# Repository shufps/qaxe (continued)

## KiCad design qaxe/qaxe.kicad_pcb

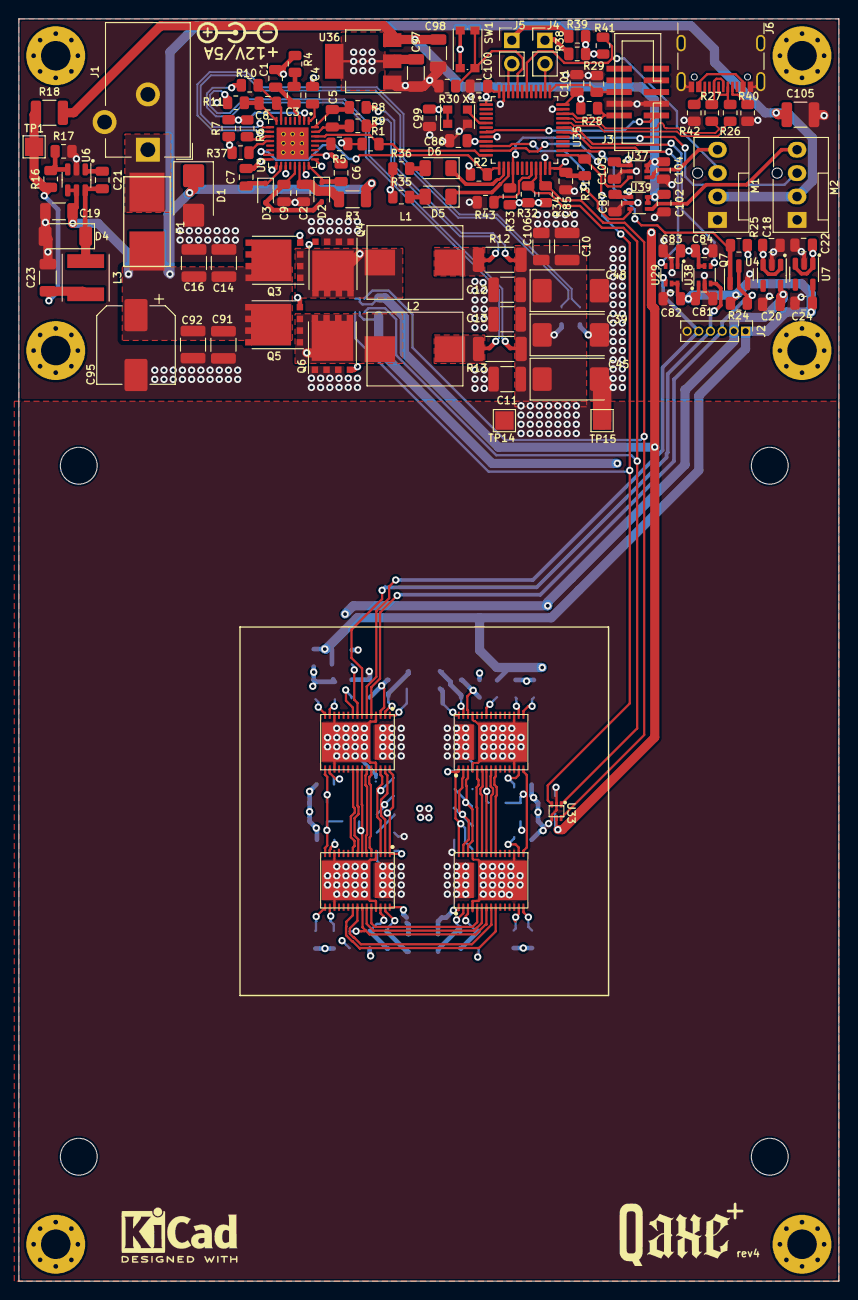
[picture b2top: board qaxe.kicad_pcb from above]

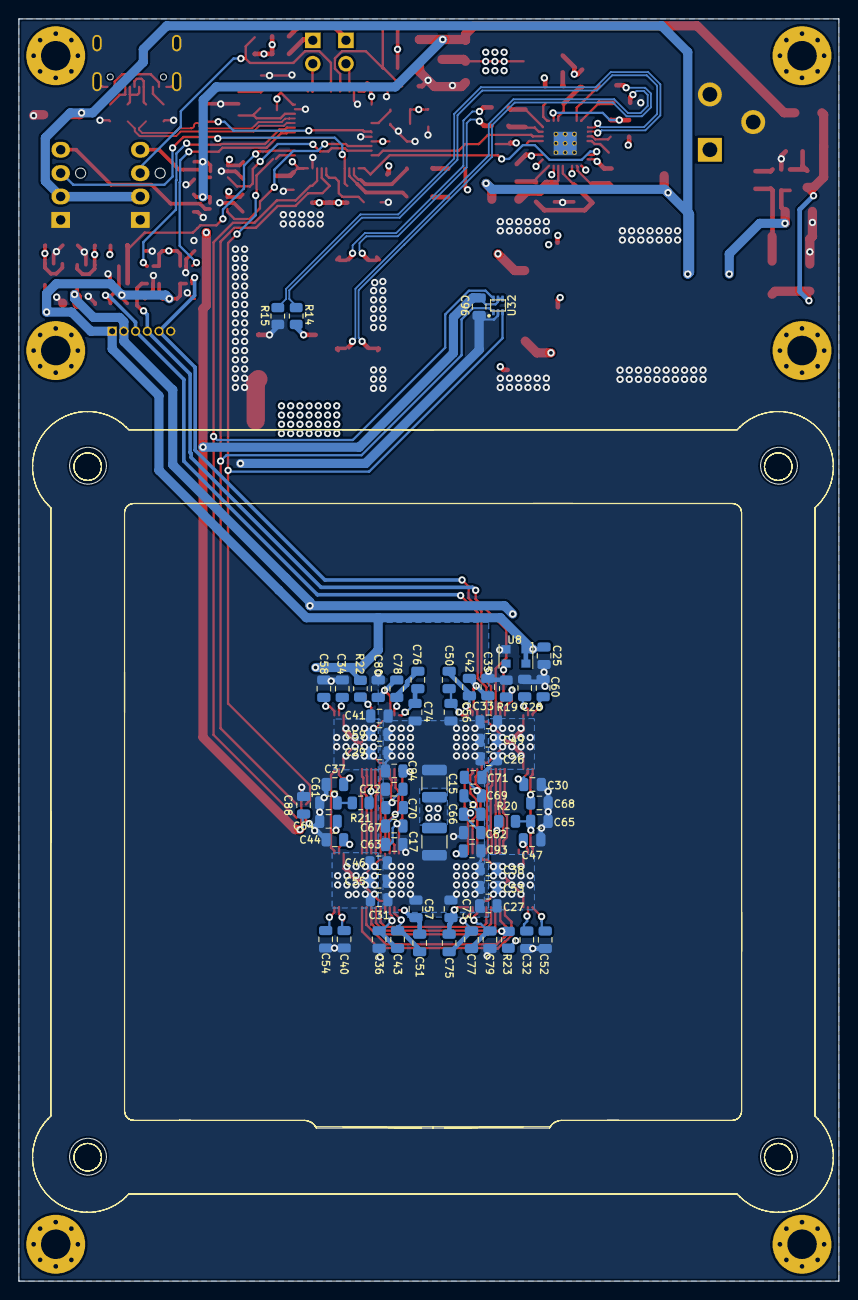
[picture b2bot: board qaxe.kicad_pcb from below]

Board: 4 copper layers, 89.0 x 137.0 mm, 198 parts (68 on the bottom side), 116 nets.

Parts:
C1: 47p; C_0805_2012Metric
C2, C4, C6, C7, C18, C22, C25, C49, C53, C55, C59, C81, C82, C83, C84, C85, C86, C87, C88, C96, C99, C100, C101, C102, C103, C104: 100n; C_0805_2012Metric
C3: 3.3n; C_0805_2012Metric
C5, C8: 1n; C_0805_2012Metric
C9: 4.7µ/25V; C_0805_2012Metric
C10, C11, C12, C13, C15, C17: 100µ/6.3V; C_1210_3225Metric
C14, C16, C91, C92, C105: 22µ/25V; C_1210_3225Metric
C19, C98: 10µF/50V; C_1206_3216Metric
C20, C24, C28, C30, C32, C33, C34, C35, C36, C37, C38, C40, C41, C42, C43, C44, C46, C47, C50, C51, C52, C54, C56, C57, C58, C60, C61, C62, C63, C64, C65, C66, C67, C68, C69, C70, C71, C72, C73, C74, C75, C76, C77, C78, C79, C80, C93, C94: 1µ; C_0805_2012Metric
C21: 10n/250V; C_0805_2012Metric
C23, C97: 22µ/16V; C_1206_3216Metric
C26, C27, C29, C31: 10µ/16V; C_0805_2012Metric
C39, C45, C48: 330µ/6.3V; CP_EIA-7343-15_Kemet-W
C95: 220µ/25V; CP_Elec_8x10
C106: 4.7µ/6.3V; C_1206_3216Metric
D1: SMBJ12A; D_SMB
D2, D3: CMDSH-3; D_SOD-323
D4: PMEG4030EP,115; D_SOD-128
D5, D6: LED; LED_1206_3216Metric
F1: 5A; fuseholder_littlefuse_blok
J1: Barrel_Jack_Switch; BarrelJack_CUI_PJ-102AH_Horizontal
J2: Conn_01x06; PinHeader_1x06_P1.27mm_Vertical
J3: SWD; PinHeader_IDC_2x05_P1.27mm_Vertical_SMD
J4, J5: Conn_01x02; PinHeader_1x02_P2.54mm_Vertical
J6: USB_C_Receptacle_USB2.0; USB_C_Receptacle_GCT_USB4105-xx-A_16P_TopMnt_Horizontal
L1, L2: 220nH; IFLR-4031GC-01-8x10
L3: 4.7µH/2A/3A; L_Taiyo-Yuden_NR-50xx
M1, M2: Fan_4pin; FanPinHeader_1x04_P2.54mm_Vertical
NT1, NT2, NT3, NT4: NetTie_2; NetTie-2_SMD_Pad0.5mm
NT7: NetTie_2; NetTie-2_L3_SMD_Pad0.5mm
Q3, Q4, Q5, Q6: CSD16415Q5T; VSONP-8-1EP_5x6_P1.27mm
Q7: BSS138; SOT-23
R1, R19, R20, R21, R22, R23, R24, R25, R28, R29, R31, R43: 10k; R_0805_2012Metric
R2, R32, R34: 1.5k; R_0805_2012Metric
R3: 2.2R; R_1206_3216Metric
R4: 8.45k; R_0805_2012Metric
R5, R30: 100k; R_0805_2012Metric
R6: 22k; R_0805_2012Metric
R7: 20k; R_0805_2012Metric
R8, R9, R10, R11: 200; R_0805_2012Metric
R12, R13: 1mR; R_2010_5025Metric
R14, R15: 10; R_0805_2012Metric
R16: 84.5k; R_0805_2012Metric
R17: 16.3k; R_0805_2012Metric
R18: 0; R_1210_3225Metric
R26, R27: 22; R_0805_2012Metric
R33, R41: 2.7k; R_0805_2012Metric
R35, R36, R38, R39: 560; R_0805_2012Metric
R37: 49.9k; R_0805_2012Metric
R40, R42: 5.1k; R_0805_2012Metric
SW1: boot; SW_Push_1P1T_NO_CK_KMR2
TP1, TP14, TP15: 3V3; TestPoint_Pad_2.0x2.0mm
U1: polarity
U3: LTC3856; QFN-32-1EP_5x5mm_P0.5mm_EP3.45x3.45mm_ThermalVias
U4: MCP1824T-0802E; SOT-23-5
U6: AP3211; SOT-23-6
U7: MCP1824T-1802E; SOT-23-5
U8: 25MHz; Oscillator_SMD_EuroQuartz_XO32-4Pin_3.2x2.5mm
U19, U20, U25, U26: BM1366_mode1; BM1368-smaller
U29, U37, U38, U39: TXU0101; SOT-363_SC-70-6
U32, U33: TMP1075; TMP1075-DRL
U35: STM32L151CCT6; LQFP-48_7x7mm_P0.5mm
U36: 1117-3.3; SOT-223-3_TabPin2
X1: 8MHz; Oscillator_SMD_EuroQuartz_XO32-4Pin_3.2x2.5mm

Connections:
+0V8: C20.1, C28.2, C30.2, C32.2, C34.2, C37.2, C40.2, C44.2, C47.2, J2.2, U4.5 (VOUT), U19.14 (VDDIO_08_0), U19.17 (VDDIO_08_1), U20.14 (VDDIO_08_0), U20.17 (VDDIO_08_1), U25.14 (VDDIO_08_0), U25.17 (VDDIO_08_1), U26.14 (VDDIO_08_0), U26.17 (VDDIO_08_1)
+1V2: C10.1, C11.1, C12.1, C13.1, C15.1, C17.1, C26.1, C27.1, C29.1, C31.1, C33.1, C38.1, C39.1, C41.1, C45.1, C46.1, C48.1, C49.1, C53.1, C55.1, C56.2, C57.2, C59.1, C62.1, C63.1, C73.1, C74.1, C93.2, C94.2, C106.1, NT3.1, NT4.2, R12.2, R13.2, R14.1, TP14.1, U19.31 (VDD), U20.31 (VDD), U25.31 (VDD), U26.31 (VDD)
+1V8: C24.1, C25.1, C52.1, C54.1, C58.1, C60.1, C61.1, C64.1, C65.1, C68.1, C81.1, C82.1, J2.1, R20.2, R21.2, R22.2, R23.2, R24.2, U7.5 (VOUT), U8.1 (Standby), U8.4 (VDD), U19.15 (VDDIO_12_0), U19.16 (VDDIO_12_1), U20.15 (VDDIO_12_0), U20.16 (VDDIO_12_1), U25.15 (VDDIO_12_0), U25.16 (VDDIO_12_1), U26.15 (VDDIO_12_0), U26.16 (VDDIO_12_1), U29.5 (OE), U29.6 (VCCB), U38.1 (VCCA)
+3V3: C18.1, C22.1, C83.1, C84.1, C85.1, C86.1, C87.1, C88.1, C96.1, C97.1, C99.1, C100.1, C101.1, C103.1, R2.1, R25.2, R28.2, R31.1, R32.1, R33.1, R34.1, R35.1, R36.1, R38.1, R39.1, R41.1, SW1.2, U4.1 (VIN), U4.3 (EN), U7.1 (VIN), U7.3 (EN), U29.1 (VCCA), U32.4 (A0), U32.5 (V+), U33.5 (V+), U35.1 (VLCD), U35.9 (VDDA), U35.24 (VDD), U35.36 (VDD), U35.48 (VDD), U36.2 (VO), U37.1 (VCCA), U38.5 (OE), U38.6 (VCCB), U39.1 (VCCA), X1.1 (EN), X1.4 (V+)
+5V: C98.1, C102.1, C104.1, R18.2, U36.3 (VI), U37.5 (OE), U37.6 (VCCB), U39.5 (OE), U39.6 (VCCB)
+12V: C14.1, C16.1, C19.1, C91.1, C92.1, C95.1, C105.1, D1.1 (A1), F1.1, M1.2 (+), M2.2 (+), Q3.3 (D), Q5.3 (D), R3.1, U6.4 (EN), U6.5 (IN)
/BM1366/BI: R19.2, U19.9 (BI)
/BM1366/CI: J2.5, U19.6 (CI), U29.4 (BY)
/BM1366/CLKI: U8.3 (Out), U19.8 (CLKI)
/BM1366/RESET: Q7.1 (G), R25.1, U35.26 (PB13)
/BM1366/RO: J2.4, U19.7 (RO), U38.3 (A)
/BM1366/RST_N: J2.3, Q7.3 (D), R24.1, U19.5 (NRSTI)
/BM1366/RXD: U35.31 (PA10), U38.4 (BY)
/BM1366/TXD: U29.3 (A), U35.30 (PA9)
/Power/1V2_PGOOD: R2.2, U3.15 (PGOOD), U35.13 (PA3)
/Power/1V2_RUN: R1.2, U3.30 (RUN), U35.12 (PA2)
/Power/DIFF+: R14.2, U3.9 (DIFFP)
/Power/DIFF-: R15.2, U3.10 (DIFFN)
/Power/SENSE1+: NT1.2, R9.1
/Power/SENSE1-: NT3.2, R8.2
/Power/SENSE2+: NT2.1, R10.2
/Power/SENSE2-: NT4.1, R11.2
/STM32/ALERT2: R31.2, U32.3 (ALERT), U33.3 (ALERT), U35.25 (PB12)
/STM32/LED1: D6.1 (K), U35.14 (PA4)
/STM32/LED2: D5.1 (K), U35.15 (PA5)
/STM32/LED3: J4.2, U35.38 (PA15)
/STM32/LED4: J5.2, U35.46 (PB9)
/STM32/NRST: J3.1, U35.7 (NRST)
/STM32/PWM1: U35.10 (PA0), U39.3 (A)
/STM32/PWM2: U35.11 (PA1), U37.3 (A)
/STM32/SCL2: R32.2, U32.1 (SCL), U33.1 (SCL), U35.21 (PB10)
/STM32/SDA2: R34.2, U32.6 (SDA), U33.6 (SDA), U35.22 (PB11)
/STM32/SWCLK: J3.6, R29.2, U35.37 (PA14)
/STM32/SWDIO: J3.2, R28.1, U35.34 (PA13)
/STM32/TACHO1: M2.3 (Tacho), R33.2, U35.16 (PA6)
/STM32/TACHO2: M1.3 (Tacho), R41.2, U35.42 (PB6)
/STM32/USB_D+: R27.1, U35.33 (PA12)
/STM32/USB_D-: R26.1, U35.32 (PA11)
/STM32/X: J6.A4 (VBUS), J6.A9 (VBUS), J6.B4 (VBUS), J6.B9 (VBUS)
GND: C2.1, C9.2, C10.2, C11.2, C12.2, C13.2, C14.2, C15.2, C16.2, C17.2, C18.2, C19.2, C20.2, C22.2, C23.2, C24.2, C25.2, C26.2, C27.2, C28.1, C29.2, C30.1, C31.2, C32.1, C33.2, C34.1, C35.1, C36.1, C37.1, C38.2, C39.2, C40.1, C41.2, C44.1, C45.2, C46.2, C47.1, C48.2, C49.2, C52.2, C53.2, C54.2, C55.2, C58.2, C59.2, C60.2, C61.2, C64.2, C65.2, C68.2, C71.2, C72.2, C79.2, C80.2, C81.2, C82.2, C83.2, C84.2, C85.2, C86.2, C87.2, C88.2, C91.2, C92.2, C95.2, C96.2, C97.2, C98.2, C99.2, C100.2, C101.2, C102.2, C103.2, C104.2, C105.2, C106.2, D1.2 (A2), D4.2 (A), J1.2, J1.3, J2.6, J3.3, J3.4, J6.A1 (GND), J6.A12 (GND), J6.B1 (GND), J6.B12 (GND), J6.S1 (SHIELD), M1.1 (-), M2.1 (-), NT7.2, Q4.1 (S), Q6.1 (S), Q7.2 (S), R15.1, R17.2, R19.1, R29.1, R30.1, R40.1, R42.1, R43.1, TP15.1, U3.33 (SGND), U4.2 (GND), U6.2 (GND), U7.2 (GND), U8.2 (GND), U19.4 (VSS), U19.13 (PLL_VSS), U19.18 (VSS), U19.27 (VSS), U19.32 (VSS), U20.4 (VSS), U20.13 (PLL_VSS), U20.18 (VSS), U20.27 (VSS), U20.32 (VSS), U25.4 (VSS), U25.13 (PLL_VSS), U25.18 (VSS), U25.27 (VSS), U25.32 (VSS), U26.4 (VSS), U26.13 (PLL_VSS), U26.18 (VSS), U26.27 (VSS), U26.32 (VSS), U29.2 (GND), U32.2 (GND), U33.2 (GND), U33.4 (A0), U35.8 (VSSA), U35.23 (VSS), U35.35 (VSS), U35.47 (VSS), U36.1 (GND), U37.2 (GND), U38.2 (GND), U39.2 (GND), X1.2 (GND)
GNDA: C1.2, C4.2, NT7.1, R1.1, R4.2, R5.1, R7.2, R37.1
unnamed: C3.2, R4.1
unnamed: C23.1, L3.2, R16.1, R18.1, TP1.1
unnamed: C9.1, D2.2 (A), D3.2 (A), U3.21 (INTVCC)
unnamed: C6.2, D2.1 (K), U3.24 (BOOST1)
unnamed: C7.1, D3.1 (K), U3.18 (BOOST2)
unnamed: C21.2, D4.1 (K), L3.1, U6.6 (SW)
unnamed: D5.2 (A), R35.2
unnamed: D6.2 (A), R36.2
unnamed: F1.2, J1.1
unnamed: J4.1, R38.2
unnamed: J5.1, R39.2
unnamed: J6.A5 (CC1), R40.2
unnamed: J6.B5 (CC2), R42.2
unnamed: J6.A6 (D+), J6.B6 (D+), R27.2
unnamed: J6.A7 (D-), J6.B7 (D-), R26.2
unnamed: L1.2, NT1.1, R12.1
unnamed: L2.2, NT2.2, R13.1
unnamed: M1.4 (PWM), U37.4 (BY)
unnamed: M2.4 (PWM), U39.4 (BY)
unnamed: Q3.2 (G), U3.25 (TG1)
unnamed: C6.1, L1.1, Q3.1 (S), Q4.3 (D), U3.26 (SW1)
unnamed: Q4.2 (G), U3.23 (BG1)
unnamed: Q5.2 (G), U3.17 (TG2)
unnamed: C7.2, L2.1, Q5.1 (S), Q6.3 (D), U3.16 (SW2)
unnamed: Q6.2 (G), U3.19 (BG2)
unnamed: R6.1, U3.11 (DIFFOUT)
unnamed: R5.2, U3.29 (FREQ)
unnamed: R37.2, U3.12 (ISET)
unnamed: C1.1, C3.1, U3.3 (ITH)
unnamed: C5.2, R9.2, U3.31 (SENSE1+)
unnamed: C5.1, R8.1, U3.32 (SENSE1-)
unnamed: C8.1, R10.1, U3.7 (SENSE2+)
unnamed: C8.2, R11.1, U3.8 (SENSE2-)
unnamed: C4.1, U3.1 (TK/SS)
unnamed: R6.2, R7.1, U3.2 (VFB)
unnamed: C2.2, R3.2, U3.22 (VIN)
unnamed: C21.1, U6.1 (BS)
unnamed: R16.2, R17.1, U6.3 (FB)
unnamed: U19.22 (BO), U25.9 (BI)
unnamed: U19.25 (CLKO), U25.6 (CI)
unnamed: U19.23 (CO), U25.8 (CLKI)
unnamed: U19.26 (NRSTO), U25.5 (NRSTI)
unnamed: R20.1, U19.24 (RI), U25.7 (RO)
unnamed: C35.2, C42.1, U19.3 (VDD1_0)
unnamed: C69.2, C71.1, U19.28 (VDD1_1), U25.3 (VDD1_0)
unnamed: C42.2, C50.1, U19.2 (VDD2_0)
unnamed: C66.2, C69.1, U19.29 (VDD2_1), U25.2 (VDD2_0)
unnamed: C50.2, C56.1, U19.1 (VDD3_0)
unnamed: C62.2, C66.1, C93.1, U19.30 (VDD3_1), U25.1 (VDD3_0)
unnamed: U20.9 (BI), U25.22 (BO)
unnamed: U20.22 (BO), U26.9 (BI)
unnamed: U20.6 (CI), U25.25 (CLKO)
unnamed: U20.8 (CLKI), U25.23 (CO)
unnamed: U20.25 (CLKO), U26.6 (CI)
unnamed: U20.23 (CO), U26.8 (CLKI)
unnamed: U20.5 (NRSTI), U25.26 (NRSTO)
unnamed: U20.26 (NRSTO), U26.5 (NRSTI)
unnamed: R21.1, U20.24 (RI), U26.7 (RO)
unnamed: R23.1, U20.7 (RO), U25.24 (RI)
unnamed: C36.2, C43.1, U20.3 (VDD1_0)
unnamed: C70.2, C72.1, U20.28 (VDD1_1), U26.3 (VDD1_0)
unnamed: C43.2, C51.1, U20.2 (VDD2_0)
unnamed: C67.2, C70.1, U20.29 (VDD2_1), U26.2 (VDD2_0)
unnamed: C51.2, C57.1, U20.1 (VDD3_0)
unnamed: C63.2, C67.1, C94.1, U20.30 (VDD3_1), U26.1 (VDD3_0)
unnamed: C77.2, C79.1, U25.28 (VDD1_1)
unnamed: C75.2, C77.1, U25.29 (VDD2_1)
unnamed: C73.2, C75.1, U25.30 (VDD3_1)
unnamed: R22.1, U26.24 (RI)
unnamed: C78.2, C80.1, U26.28 (VDD1_1)
unnamed: C76.2, C78.1, U26.29 (VDD2_1)
unnamed: C74.2, C76.1, U26.30 (VDD3_1)
unnamed: R30.2, SW1.1, U35.44 (BOOT0)
unnamed: R43.2, U35.20 (PB2)
unnamed: U35.5 (PH0), X1.3 (OUT)

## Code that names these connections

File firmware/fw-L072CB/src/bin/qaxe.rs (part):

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
    let p = embassy_stm32::init(config);

    let driver = Driver::new(p.USB, Irqs, p.PA12, p.PA11);

    // Create embassy-usb Config
    let mut config = embassy_usb::Config::new(0xc0de, 0xcaff);
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    let mut tx_buf = [0u8; TX_BUF_SIZE];
    let mut rx_buf = [0u8; RX_BUF_SIZE];

    let usart = BufferedUart::new(p.USART1, Irqs, p.PA10, p.PA9, &mut tx_buf, &mut rx_buf, config).unwrap();
    let (mut tx_ctrl, mut rx_ctrl) = usart.split();

    // Run the USB device.
    let usb_fut = usb.run();

    let run_1v2 = Output::new(p.PA2, Level::Low, Speed::Low);
    let pgood_1v2 = Input::new(p.PA3, Pull::None);
    let pgood_led = Output::new(p.PA5, Level::High, Speed::Low);
    let mut activity_led = Output::new(p.PA4, Level::High, Speed::Low);

    // init ldo_en with low
    let ldo_en = Output::new(p.PA7, Level::Low, Speed::Low);

    let reset = Output::new(p.PB13, Level::High, Speed::Low);

    let ch1 = PwmPin::new_ch1(p.PA0, OutputType::PushPull);
    let ch2 = PwmPin::new_ch2(p.PA1, OutputType::PushPull);
    let mut pwm1 = SimplePwm::new(
        p.TIM2,
        Some(ch1),
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
    let i2c = I2c::new(
        p.I2C2,
        p.PB10,
        p.PB11,
        Irqs,
        p.DMA1_CH4,
        p.DMA1_CH5,
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
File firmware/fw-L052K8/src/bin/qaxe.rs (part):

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
    let p = embassy_stm32::init(config);

    let driver = Driver::new(p.USB, Irqs, p.PA12, p.PA11);

    // Create embassy-usb Config
    let mut config = embassy_usb::Config::new(0xc0de, 0xcaff);
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    static RX_BUF: StaticCell<[u8; 64]> = StaticCell::new();
    let rx_buf = &mut RX_BUF.init([0; 64])[..];

    let usart = BufferedUart::new(p.USART1, Irqs, p.PA10, p.PA9, tx_buf, rx_buf, config).unwrap();
    let (mut tx_ctrl, mut rx_ctrl) = usart.split();

    // Run the USB device.
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
    let run_1v2 = Output::new(p.PB0, Level::Low, Speed::Low);
    let pgood_1v2 = Input::new(p.PB1, Pull::None);
    let pgood_led = Output::new(p.PA6, Level::High, Speed::Low);

    let reset = Output::new(p.PA8, Level::High, Speed::Low);

    let ch1 = PwmPin::new_ch1(p.PA0, OutputType::PushPull);
    let mut pwm1 = SimplePwm::new(p.TIM2, Some(ch1), None, None, None, khz(10), Default::default());
    pwm1.set_polarity(PWMChannel::Ch1, OutputPolarity::ActiveLow);
    pwm1.set_duty(PWMChannel::Ch1, pwm1.get_max_duty());
    pwm1.enable(PWMChannel::Ch1);

    let i2c = I2c::new(p.I2C1, p.PB6, p.PB7, Irqs, NoDma, NoDma, Hertz(100_000), Default::default());


    unwrap!(spawner.spawn(reset_manager(reset)));
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
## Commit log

2024-01-15 initial commit (rev2)
2024-01-15 updated bom and gerbers
2024-01-15 added firmware for rev1 and rev2
2024-01-15 fixed bom
2024-01-15 fixed compilation rev1
2024-01-15 fixed compilation rev2
2024-01-15 Create LICENSE
2024-01-16 updated BOM and replaces bss138 and 3.3V LDO with parts that are available
2024-01-17 switched to buffered uart
2024-01-21 rev3
2024-01-24 replaced 20k with 22k on feedback voltage divider to increase core voltage by 0.05V. 485MHz working properly now at 100% cooling
2024-01-26 fixed broken bom
2024-01-27 made pwm2 work, cargo clippy & fmt
2024-01-27 switched dma uart to buffereduart
2024-01-29 updated ibom
2024-01-30 4.7u cap was missing in digikey bom
2024-02-02 added run.sh scripts for fw rev1 and rev2
2024-02-14 fixed wrong lm1117 variant in bom
2024-02-14 removed temporary changes from rev2 fw
2024-02-14 firmware for testing
2024-02-21 rev2 fw fix, added resyncing to preamble
2024-02-22 bigger stm32 variant that has usb bootloader
2024-02-22 fw-rev3 (with stm32l151cc - only change)
2024-02-22 updated bom and ibom for stm32l151cc
2024-02-22 updated ibom with -CC variant
2024-02-22 updated board with -CC variant
2024-02-27 3d design files (back missing, comes later)
2024-02-27 added case
2024-03-04 v0.31
2024-03-04 back of case added
2024-03-12 rev3.2
2024-03-12 added points for pin 1 on Us
2024-03-26 1368 support
2024-03-26 gerbers for 1368
2024-04-01 restructured
2024-04-01 restructured firmware directory
2024-04-01 updated stm32 to L072 on normal qaxe
2024-04-01 updated qaxe+ to L072
2024-04-19 Update README.md
    fixed cargo objcopy
2024-05-03 qaxe+
2024-05-03 updated L151 with L072 for qaxe+
2024-05-03 some bom fixes
2024-05-15 rev4.1 qaxe+ (added pull downs on NRSTI)
2024-05-15 improvements on power managemend and reset for qaxe+
2024-05-15 Update LICENSE
2024-06-10 fixed uid
2024-08-06 backported latest qaxe+ version to L151c8
2024-08-12 added .gitignore
2024-08-12 removed old firmware
2024-08-12 initial nerdqaxe+
2024-08-12 nerdqax+ digikey bom
2024-08-18 removed big M4 connectors because they were only for the prototypes
2024-09-27 removed ph2-dis solderjumper because it's not needed
2024-10-18 initial ++ commit
2024-10-18 gerbers
2024-10-18 added jlc settings
2024-10-18 ibom and digikey order list
2024-10-18 updated fuse to 8A
2024-10-18 added holes for another cooler
2024-12-08 added measurements
2025-01-02 digikey bom with refs
2025-01-07 switched to 6 layer, lga1700 instead of lga115x holes
2025-01-07 added new layers
2025-02-17 fixed temp sensing connection to the buck on the ++
2025-03-20 removed solder jumper on ++
2025-03-21 removed solderjumpers on ++
2025-04-09 updated 220uF on ++ to 25V
2025-04-09 updated bom of + for 24V cap
2025-04-09 fixed wrong value
2025-04-09 updated ibom with updated R value
2025-04-26 disabled weird lga115x heatsinks in 3d view
2026-01-11 moved old qaxes to legaxy
2026-01-11 rev5.1.1
2026-01-11 Fix formatting in README for previous version note
2026-01-15 disabled FCCM
